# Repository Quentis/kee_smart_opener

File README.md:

# kee_smart_opener

## Reference documents

The datasheets and manuals are not stored in the repository, the table below links to the manufacturers' copies.
The one exception is the E07-433M20S user manual, which is hard to find online and is kept in
[`doc/`](doc/E07-433M20S_Usermanual_EN_v1.30.pdf).

| Document | Notes |
|---|---|
| [HCS300 KEELOQ Code Hopping Encoder datasheet](https://ww1.microchip.com/downloads/en/DeviceDoc/21137G.pdf) | Microchip DS21137G |
| [CC1101 Low-Power Sub-1 GHz RF Transceiver datasheet](https://www.ti.com/lit/ds/symlink/cc1101.pdf) | The transceiver on the E07-433M20S module |
| [RP2350 datasheet](https://datasheets.raspberrypi.com/rp2350/rp2350-datasheet.pdf) | MCU of `sw/kso-fw-rs` |
| [EFR32FG23 Wireless SoC Family Data Sheet](https://www.silabs.com/documents/public/data-sheets/efr32fg23-datasheet.pdf) | Rev. 1.4, SoC of `sw/efr32fg23` |
| [EFR32xG23 Wireless SoC Reference Manual](https://www.silabs.com/documents/public/reference-manuals/efr32xg23-rm.pdf) | Rev. 1.1 |
| [BRD4002A Wireless Pro Kit Mainboard schematic](https://www.silabs.com/documents/public/schematic-files/BRD4002A-A07-schematic.pdf) | Rev. A07 |
| [BRD4265B EFR32FG23B Radio Board (434 MHz, 10 dBm) schematic](https://www.silabs.com/documents/public/schematic-files/BRD4265B-A00-schematic.pdf) | Rev. A00, the copy that was in the repository was A01 |

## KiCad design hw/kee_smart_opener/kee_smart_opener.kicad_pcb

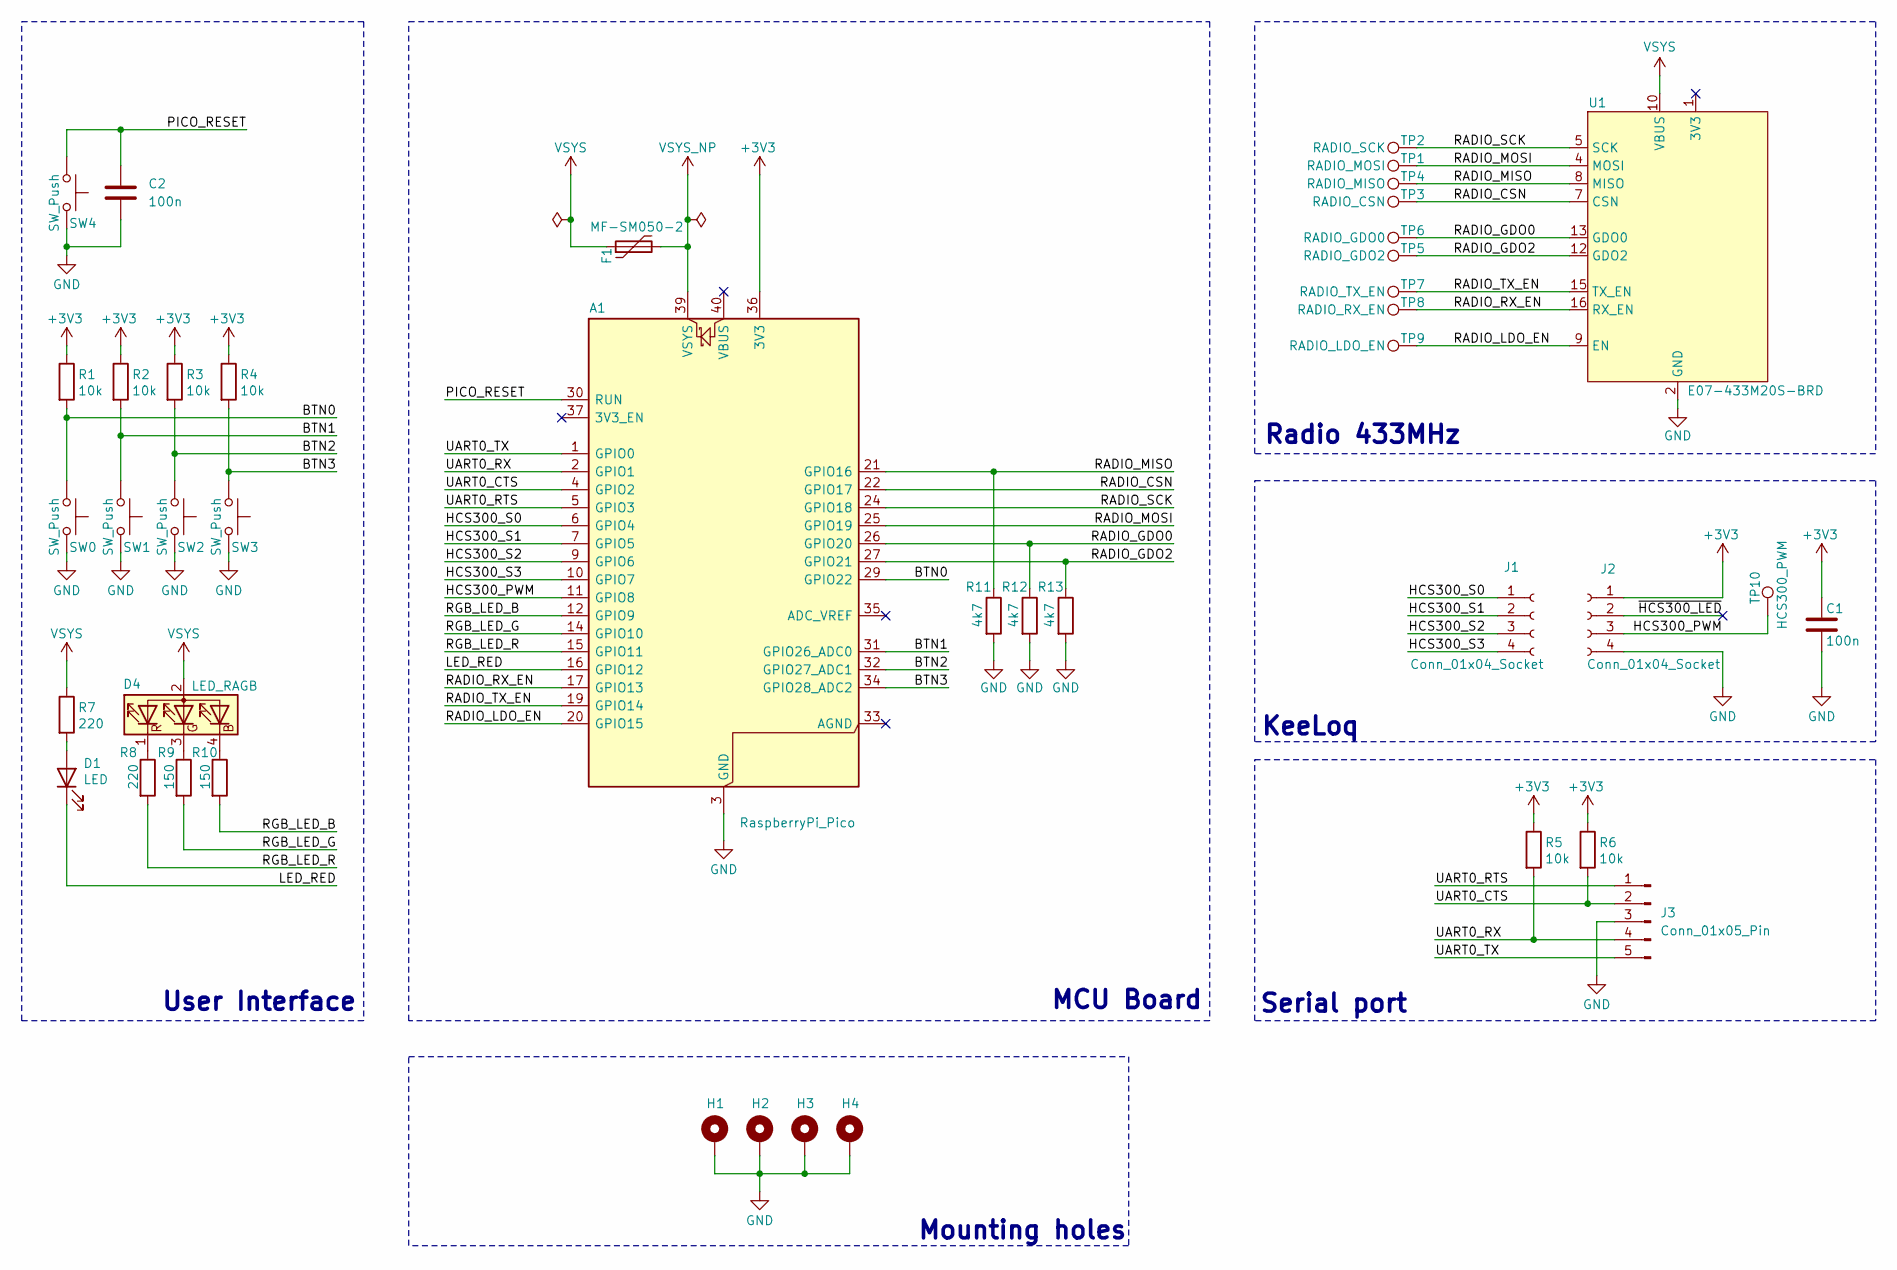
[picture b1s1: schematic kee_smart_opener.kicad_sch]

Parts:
A1: RaspberryPi_Pico; RaspberryPi_Pico_Common_THT
C1, C2: 100n; C_0603_1608Metric_Pad1.08x0.95mm_HandSolder
D1: LED; LED_D5.0mm
D4: LED_RAGB; LED_D5.0mm-4_RGB
F1: MF-SM050-2; Fuse_Bourns_MF-SM_7.98x5.44mm
H1, H2, H3, H4: MountingHole_Pad; MountingHole_3.5mm_Pad_Via
J1, J2: Conn_01x04_Socket; PinSocket_1x04_P2.54mm_Vertical
J3: Conn_01x05_Pin; PinHeader_1x05_P2.54mm_Horizontal
R1, R2, R3, R4, R5, R6: 10k; R_0603_1608Metric_Pad0.98x0.95mm_HandSolder
R7, R8: 220; R_0603_1608Metric_Pad0.98x0.95mm_HandSolder
R9, R10: 150; R_0603_1608Metric_Pad0.98x0.95mm_HandSolder
R11, R12, R13: 4k7; R_0603_1608Metric_Pad0.98x0.95mm_HandSolder
SW0, SW1, SW2, SW3, SW4: SW_Push; SW_B3F-3100
TP1: RADIO_MOSI; TestPoint_Pad_D1.5mm
TP2: RADIO_SCK; TestPoint_Pad_D1.5mm
TP3: RADIO_CSN; TestPoint_Pad_D1.5mm
TP4: RADIO_MISO; TestPoint_Pad_D1.5mm
TP5: RADIO_GDO2; TestPoint_Pad_D1.5mm
TP6: RADIO_GDO0; TestPoint_Pad_D1.5mm
TP7: RADIO_TX_EN; TestPoint_Pad_D1.5mm
TP8: RADIO_RX_EN; TestPoint_Pad_D1.5mm
TP9: RADIO_LDO_EN; TestPoint_Pad_D1.5mm
TP10: HCS300_PWM; TestPoint_Pad_D1.5mm
U1: E07-433M20S-BRD

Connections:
+3V3: A1.36 (3V3), C1.1, J2.1, R1.1, R2.1, R3.1, R4.1, R5.1, R6.1
/BTN0: A1.29 (GPIO22), R1.2, SW0.2
/BTN1: A1.31 (GPIO26_ADC0), R2.2, SW1.2
/BTN2: A1.32 (GPIO27_ADC1), R3.2, SW2.2
/BTN3: A1.34 (GPIO28_ADC2), R4.2, SW3.2
/HCS300_PWM: A1.11 (GPIO8), J2.3, TP10.1 (1_1)
/HCS300_S0: A1.6 (GPIO4), J1.1
/HCS300_S1: A1.7 (GPIO5), J1.2
/HCS300_S2: A1.9 (GPIO6), J1.3
/HCS300_S3: A1.10 (GPIO7), J1.4
/LED_RED: A1.16 (GPIO12), D1.1 (K)
/PICO_RESET: A1.30 (RUN), C2.1, SW4.2
/RADIO_CSN: A1.22 (GPIO17), TP3.1 (1_1), U1.7 (CSN)
/RADIO_GDO0: A1.26 (GPIO20), R12.1, TP6.1 (1_1), U1.13 (GDO0)
/RADIO_GDO2: A1.27 (GPIO21), R13.1, TP5.1 (1_1), U1.12 (GDO2)
/RADIO_LDO_EN: A1.20 (GPIO15), TP9.1 (1_1), U1.9 (EN)
/RADIO_MISO: A1.21 (GPIO16), R11.1, TP4.1 (1_1), U1.8 (MISO)
/RADIO_MOSI: A1.25 (GPIO19), TP1.1 (1_1), U1.4 (MOSI)
/RADIO_RX_EN: A1.17 (GPIO13), TP8.1 (1_1), U1.16 (RX_EN)
/RADIO_SCK: A1.24 (GPIO18), TP2.1 (1_1), U1.5 (SCK)
/RADIO_TX_EN: A1.19 (GPIO14), TP7.1 (1_1), U1.15 (TX_EN)
/RGB_LED_B: A1.12 (GPIO9), R10.2
/RGB_LED_G: A1.14 (GPIO10), R9.2
/RGB_LED_R: A1.15 (GPIO11), R8.2
/UART0_CTS: A1.4 (GPIO2), J3.2, R6.2
/UART0_RTS: A1.5 (GPIO3), J3.1
/UART0_RX: A1.2 (GPIO1), J3.4, R5.2
/UART0_TX: A1.1 (GPIO0), J3.5
/~HCS300_LED: J2.2
GND: A1.3 (GND), A1.8 (GND), A1.13 (GND), A1.18 (GND), A1.23 (GND), A1.28 (GND), A1.38 (GND), C1.2, C2.2, H1.1 (1_1), H2.1 (1_1), H3.1 (1_1), H4.1 (1_1), J2.4, J3.3, R11.2, R12.2, R13.2, SW0.1, SW1.1, SW2.1, SW3.1, SW4.1, U1.2 (GND), U1.3 (GND), U1.6 (GND), U1.11 (GND), U1.14 (GND)
unnamed: D1.2 (A), R7.2
unnamed: D4.4 (BK), R10.1
unnamed: D4.3 (GK), R9.1
unnamed: D4.1 (RK), R8.1
VSYS: D4.2 (A), F1.1, R7.1, U1.10 (VBUS)
VSYS_NP: A1.39 (VSYS), F1.2

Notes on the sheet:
Serial port
Radio 433MHz
User Interface
KeeLoq
Mounting holes
MCU Board

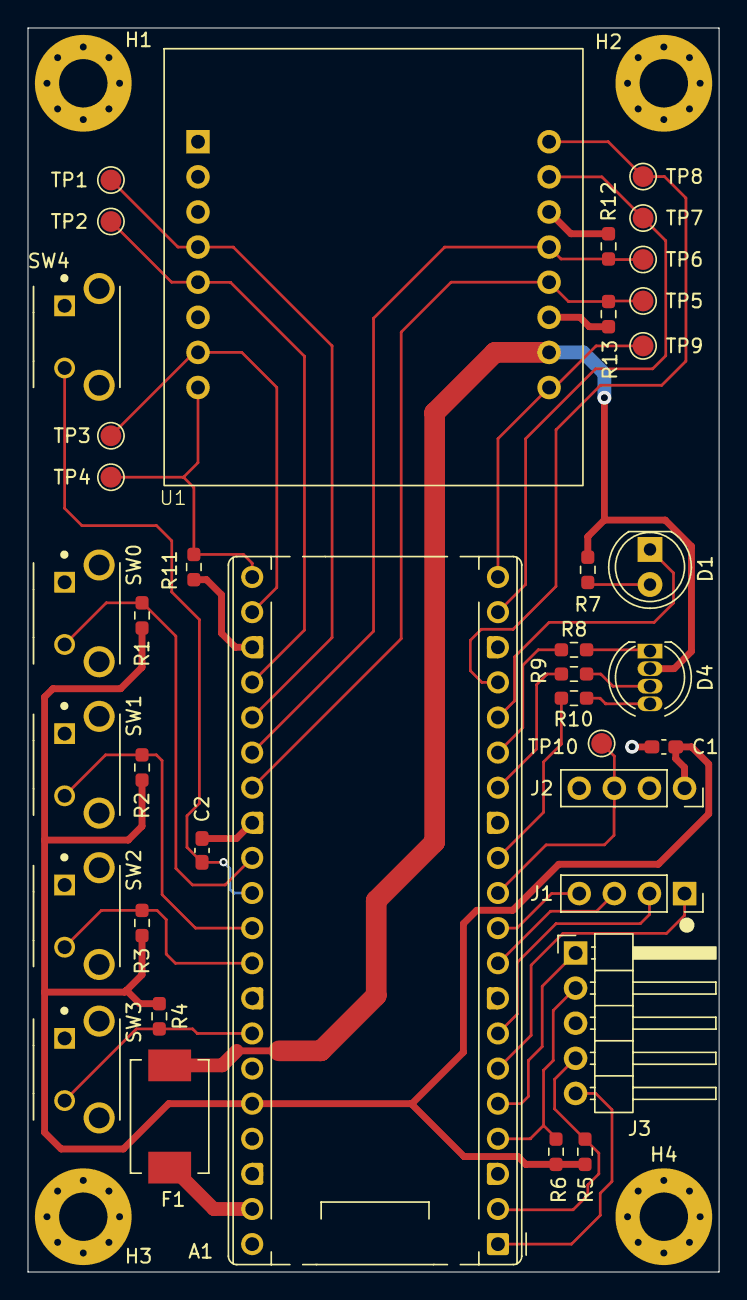
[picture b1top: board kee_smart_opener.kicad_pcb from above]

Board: 2 copper layers, 50.0 x 90.0 mm, 42 parts (0 on the bottom side), 35 nets.

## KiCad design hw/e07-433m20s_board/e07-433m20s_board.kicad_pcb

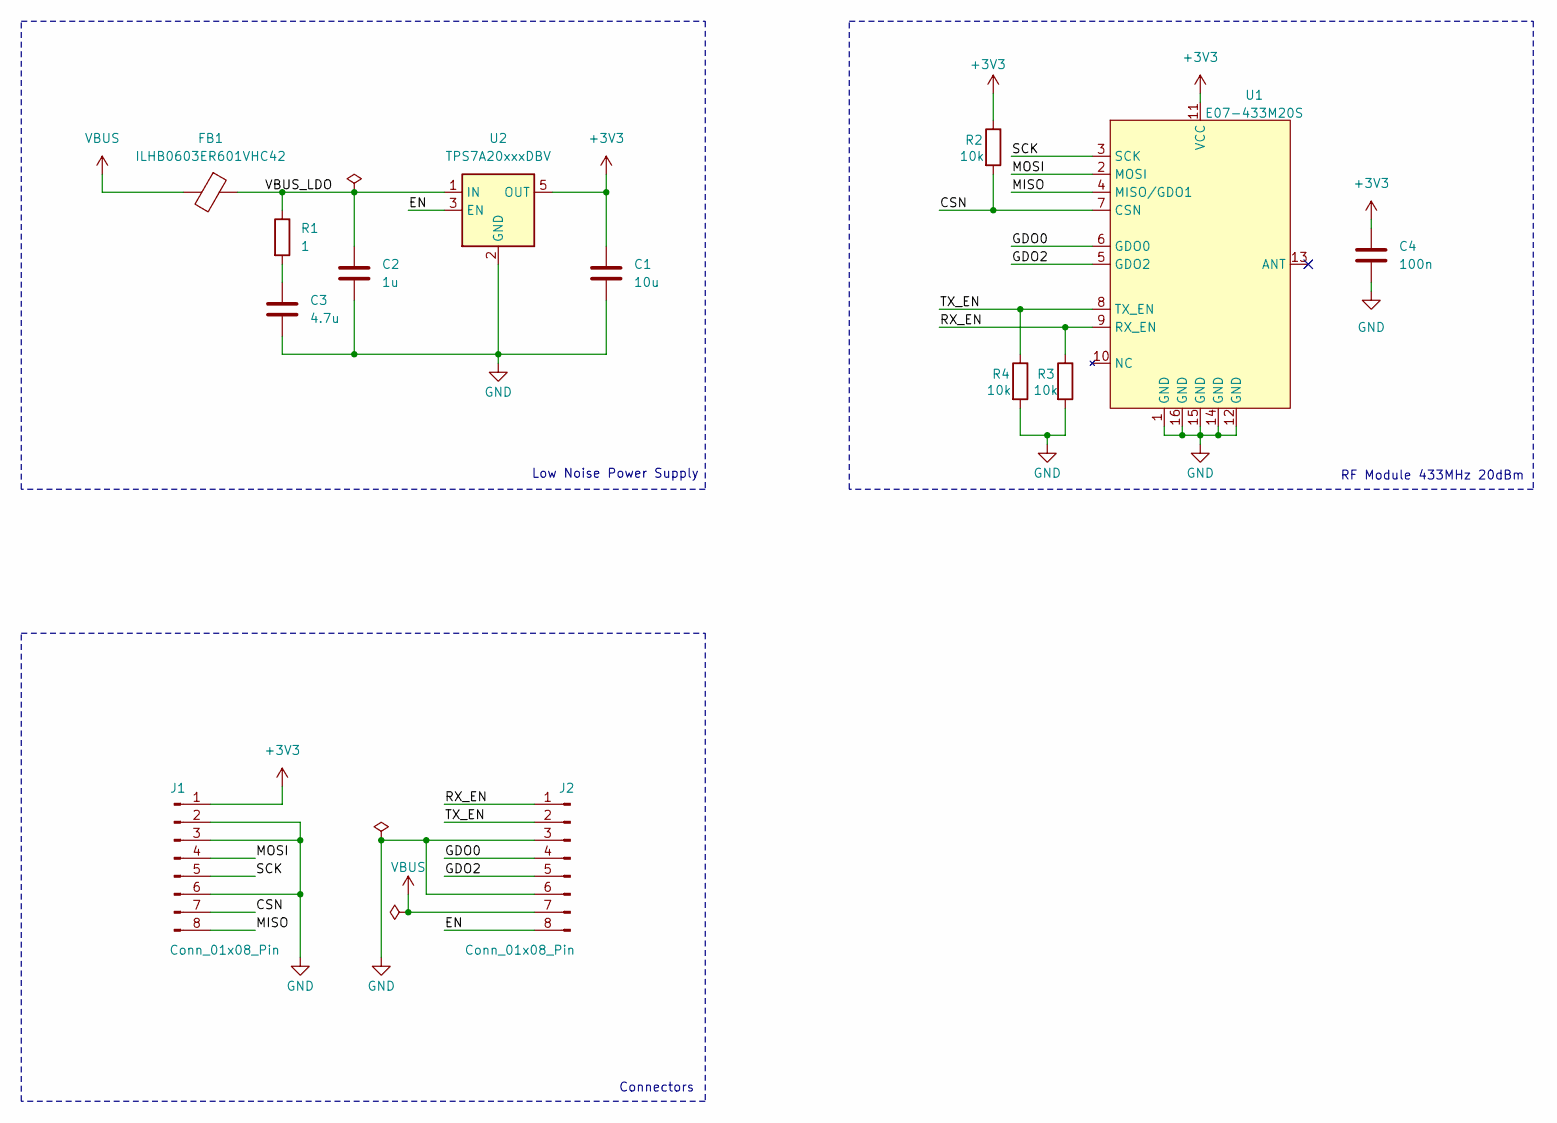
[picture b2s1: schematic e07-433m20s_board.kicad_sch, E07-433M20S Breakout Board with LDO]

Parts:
C1: 10u; C_0805_2012Metric_Pad1.18x1.45mm_HandSolder
C2: 1u; C_0603_1608Metric_Pad1.08x0.95mm_HandSolder
C3: 4.7u; C_0805_2012Metric_Pad1.18x1.45mm_HandSolder
C4: 100n; C_0603_1608Metric_Pad1.08x0.95mm_HandSolder
FB1: ILHB0603ER601VHC42; L_0603_1608Metric
J1, J2: Conn_01x08_Pin; PinHeader_1x08_P2.54mm_Vertical
R1: 1; R_0603_1608Metric_Pad0.98x0.95mm_HandSolder
R2, R3, R4: 10k; R_0603_1608Metric_Pad0.98x0.95mm_HandSolder
U1: E07-433M20S
U2: TPS7A20xxxDBV; SOT-23-5

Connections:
+3V3: C1.1, C4.1, J1.1, R2.1, U1.11 (VCC), U2.5 (OUT)
/CSN: J1.7, R2.2, U1.7 (CSN)
/EN: J2.8, U2.3 (EN)
/GDO0: J2.4, U1.6 (GDO0)
/GDO2: J2.5, U1.5 (GDO2)
/MISO: J1.8, U1.4 (MISO/GDO1)
/MOSI: J1.4, U1.2 (MOSI)
/RX_EN: J2.1, R3.1, U1.9 (RX_EN)
/SCK: J1.5, U1.3 (SCK)
/TX_EN: J2.2, R4.1, U1.8 (TX_EN)
/VBUS_LDO: C2.1, FB1.1, R1.1, U2.1 (IN)
GND: C1.2, C2.2, C3.2, C4.2, J1.2, J1.3, J1.6, J2.3, J2.6, R3.2, R4.2, U1.1 (GND), U1.12 (GND), U1.14 (GND), U1.15 (GND), U1.16 (GND), U2.2 (GND)
unnamed: C3.1, R1.2
VBUS: FB1.2, J2.7

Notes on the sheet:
Connectors
RF Module 433MHz 20dBm
Low Noise Power Supply

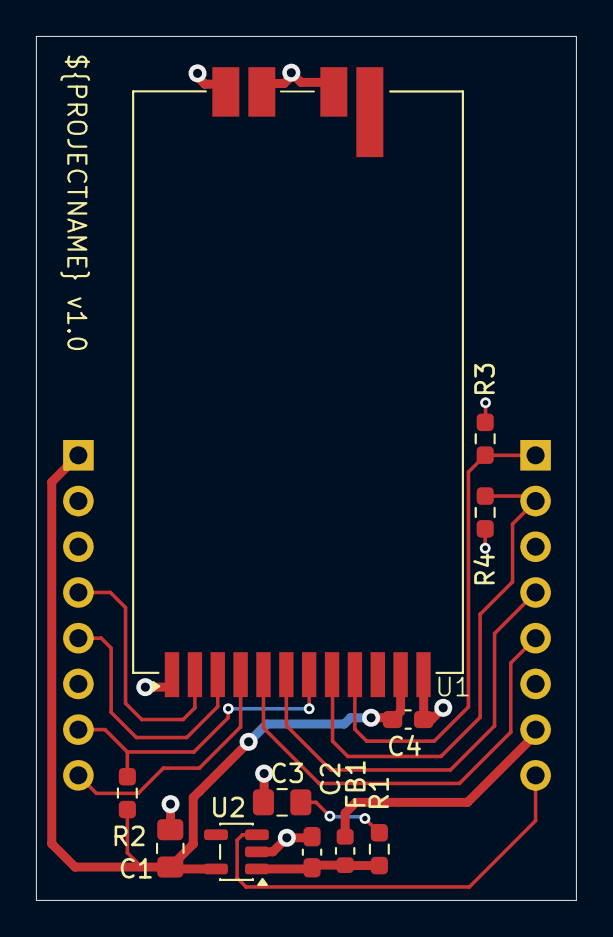
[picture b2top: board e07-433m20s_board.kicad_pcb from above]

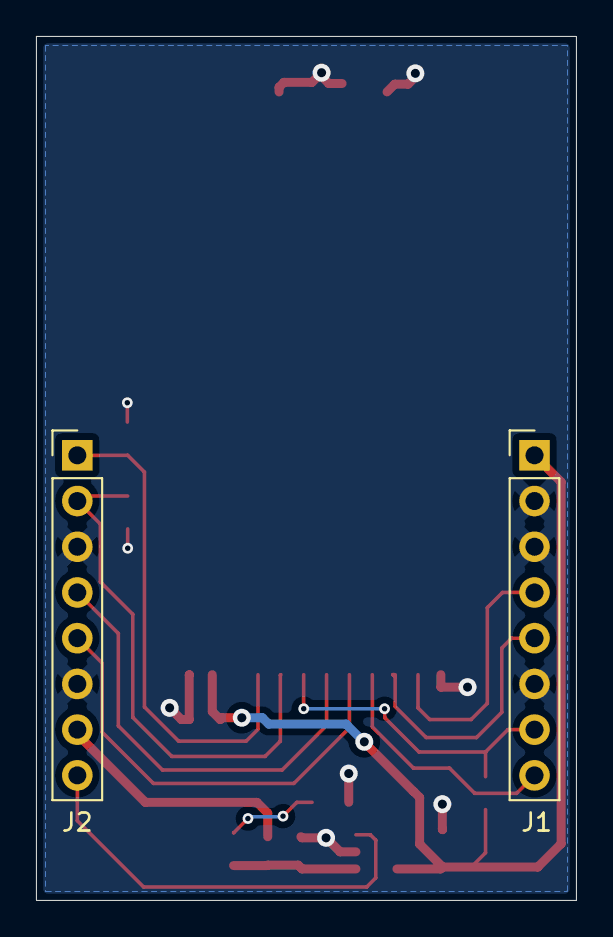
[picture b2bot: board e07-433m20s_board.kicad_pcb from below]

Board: 2 copper layers, 30.0 x 48.0 mm, 13 parts (2 on the bottom side), 14 nets.

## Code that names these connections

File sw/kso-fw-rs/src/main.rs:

#![no_std]
#![no_main]
#![allow(unused)]

use cc1101_embassy::{Cc1101, Modulation, PacketLength, RadioConfig, SyncMode, TxPower};
use defmt as _;
use defmt::{debug, error, info, warn};
use defmt_rtt as _;
use embassy_embedded_hal::shared_bus::asynch::spi::SpiDevice;
use embassy_executor::Spawner;
use embassy_rp::gpio::{Input, Level, Output, Pull};
use embassy_rp::peripherals::{DMA_CH0, DMA_CH1, PIO0};
use embassy_rp::pio::program::pio_file;
use embassy_rp::pio::{Common, FifoJoin, Pio, PioPin, StateMachine};
use embassy_rp::pio_programs::clock_divider::calculate_pio_clock_divider;
use embassy_rp::spi::{self, Phase, Polarity, Spi};
use embassy_rp::{Peri, binary_info, pio};
use embassy_rp::{bind_interrupts, dma};
use embassy_sync::blocking_mutex::raw::NoopRawMutex;
use embassy_sync::mutex::Mutex;
use embassy_time::{Instant, Timer};
use embedded_hal_async::spi::{Operation, SpiDevice as _};
use fugit::{ExtU32, Hertz, HertzU32, RateExtU32};
use panic_probe as _;
use static_cell::StaticCell;

mod hcs300;
use hcs300::{Hcs300Decoder, Hcs300Packet};

use crate::hcs300::{Hcs300ButtonStatus, Hcs300SerialNumber};

type AsyncSpi0 = Spi<'static, embassy_rp::peripherals::SPI0, spi::Async>;

static SPI_BUS: StaticCell<Mutex<NoopRawMutex, AsyncSpi0>> = StaticCell::new();

bind_interrupts!(struct Irqs {
    DMA_IRQ_0 => dma::InterruptHandler<DMA_CH0>, dma::InterruptHandler<DMA_CH1>;
    PIO0_IRQ_0 => pio::InterruptHandler<PIO0>;
});

/// Idle/stuck timeout of the HCS300 PIO program in ticks (1 tick = 1 us). Has to be longer than the
/// longest legitimate pulse, which is the header (10 TE, up to 6.6 ms).
const HCS300_TIMEOUT_TICKS: u32 = 10_000;

/// Word pushed by the HCS300 PIO program when the line was idle or stuck for the whole timeout
const HCS300_PIO_SENTINEL: u32 = u32::MAX;

/// Measures the high and low pulses of the HCS300 PWM output.
///
/// For every edge one word is pushed to the RX FIFO: the ticks left of the timeout counter, so the
/// pulse duration is `HCS300_TIMEOUT_TICKS - word`. If the line stays at one level for the whole
/// timeout, `HCS300_PIO_SENTINEL` is pushed instead (and a stuck high line is waited out).
///
/// The program and its cycle budget are in `pio/hcs300_capture.pio`. One tick is 5 PIO cycles (5 MHz
/// clock). The simulation tests in `test/sim/pio` read the same file.
fn setup_pio_task_sm0<'d>(
    pio: &mut Common<'d, PIO0>,
    sm: &mut StateMachine<'d, PIO0, 0>,
    hcs300_pwm_pin: Peri<'d, impl PioPin>,
) {
    let prog = pio_file!("pio/hcs300_capture.pio");
    let mut cfg = pio::Config::default();
    let loaded_prog = &pio.load_program(&prog.program);
    debug!("HCS300 PIO0 origin: {}", loaded_prog.origin);
    cfg.use_program(loaded_prog, &[]);
    let in_pin = pio.make_pio_pin(hcs300_pwm_pin);
    cfg.set_in_pins(&[&in_pin]);
    cfg.set_jmp_pin(&in_pin);
    cfg.clock_divider = calculate_pio_clock_divider(5_000_000);
    sm.set_config(&cfg);
}

#[embassy_executor::task]
async fn pio_task_sm0(mut sm: StateMachine<'static, PIO0, 0>) {
    sm.set_enable(true);

    sm.tx().push(HCS300_TIMEOUT_TICKS);
    let mut decoder = Hcs300Decoder::new();
    loop {
        let word = sm.rx().wait_pull().await;
        if word == HCS300_PIO_SENTINEL {
            decoder.reset();
            continue;
        }

        let ticks = HCS300_TIMEOUT_TICKS.saturating_sub(word);
        if let Some(packet) = decoder.push(ticks) {
            info!(
                "HCS300: serial {=u32:08x}, buttons {=u8:04b}, vlow {}, repeat {}, encrypted {=u32:08x}, TE {} us",
                packet.serial_number.get(),
                packet.button_status.get(),
                packet.vlow,
                packet.repeat,
                packet.encrypted,
                decoder.te()
            );
        }
    }
}

#[embassy_executor::main]
async fn main(spawner: Spawner) {
    info!("Starting...");
    let p = embassy_rp::init(Default::default());

    // let mut led_rgb_blue = Output::new(p.PIN_9, Level::Low);
    // let mut led_rgb_green = Output::new(p.PIN_10, Level::Low);
    // let mut led_rgb_red = Output::new(p.PIN_11, Level::Low);

    // let mut led_err_red = Output::new(p.PIN_12, Level::Low);

    let mut led_run_green = Output::new(p.PIN_25, Level::High);

    // Configure HCS300 pins
    let mut hcs300_pwm_pin = p.PIN_8;
    let mut pio = Pio::new(p.PIO0, Irqs);

    // // Configure CC1101 pins
    // let mut cc1101_en = Output::new(p.PIN_15, Level::Low);
    // let mut cc1101_tx_en = Output::new(p.PIN_14, Level::Low);
    // let mut cc1101_rx_en = Output::new(p.PIN_13, Level::Low);

    // let mut spi_config = spi::Config::default();
    // spi_config.frequency = 1_000_000;
    // spi_config.phase = Phase::CaptureOnFirstTransition;
    // spi_config.polarity = Polarity::IdleLow;

    // let cs = Output::new(p.PIN_17, Level::High);

    // // Enable the LDO on e07-433m20s_board (C1101 chip)
    // cc1101_en.set_high();

    // let spi_bus = Spi::new(
    //     p.SPI0, p.PIN_18, p.PIN_19, p.PIN_16, p.DMA_CH0, p.DMA_CH1, Irqs, spi_config,
    // );
    // let spi_bus = SPI_BUS.init(Mutex::new(spi_bus));
    // let mut spi_dev = SpiDevice::new(spi_bus, cs);

    // let mut btn0 = Input::new(p.PIN_22, Pull::None);

    // let gdo0 = Input::new(p.PIN_20, Pull::None);
    // let gdo2 = Input::new(p.PIN_21, Pull::None);

    // let packet = Hcs300Packet {
    //     encrypted: 0,
    //     serial_number: Hcs300SerialNumber::new(0).unwrap(),
    //     button_status: Hcs300ButtonStatus::new(0).unwrap(),
    //     vlow: false,
    //     repeat: false,
    // };
    // let mut encoded_packet = [0; Hcs300Packet::CODEWORD_BYTES];
    // packet
    //     .encode(&mut encoded_packet)
    //     .expect("Keeloq packet encoding failed!");

    // let mut cc1101 = match Cc1101::new(spi_dev, gdo0, gdo2).await {
    //     Ok(dev) => dev,
    //     Err(e) => {
    //         error!("CC1101 init failed: {:?}", e);
    //         loop {
    //             Timer::after_millis(1000).await;
    //         }
    //     }
    // };

    // let radio_config = RadioConfig::new()
    //     .frequency_hz(433_920_000)
    //     .baud_rate(2500)
    //     .modulation(Modulation::Ook)
    //     .sync_mode(SyncMode::None)
    //     .sync_word(0xD391)
    //     .packet_length(PacketLength::Fixed(Hcs300Packet::CODEWORD_BYTES as u8))
    //     .append_status(false)
    //     .crc_enable(false)
    //     .tx_power(TxPower::DbmMinus10);

    // if let Err(spi_err) = cc1101.configure(&radio_config).await {
    //     error!("SPI error during configure: {:?}", spi_err);
    //     loop {
    //         Timer::after_millis(1000).await;
    //     }
    // }

    // if let Err(err) = cc1101.idle().await {
    //     error!("Error during idle transition: {:?}", err)
    // }

    setup_pio_task_sm0(&mut pio.common, &mut pio.sm0, hcs300_pwm_pin);
    spawner.spawn(pio_task_sm0(pio.sm0).unwrap());

    loop {
        // btn0.wait_for_low().await;
        // info!("Button 0 pressed");
        // btn0.wait_for_high().await;

        //     let mut buf = [0u8; 1];
        //     spi_dev
        //         .transaction(&mut [
        //             Operation::Write(&[0x31 | 0x80 | 0x40]),
        //             Operation::Read(&mut buf),
        //         ])
        //         .await
        //         .unwrap();
        //     info!("Version number: {}", buf);
        // Timer::after_millis(100).await;
        // let test_packet = [0x55; 5];

        // Test cc1101
        // cc1101_tx_en.set_high();
        // Timer::after_millis(10).await;
        // let tx_start = Instant::now();
        // let tx_result = cc1101.transmit(&encoded_packet[..]).await;
        // info!("transmit took {} ms", tx_start.elapsed().as_millis());
        // match tx_result {
        //     Ok(()) => {
        //         info!("Keeloq packet transmitted: {=[u8]:02x}", encoded_packet[..])
        //     }
        //     Err(err) => {
        //         error!("Error during transmission: {:?}", err)
        //     }
        // }
        // Timer::after_millis(10).await;
        // cc1101_tx_en.set_low();

        // if let Err(err) = cc1101.idle().await {
        //     error!("Error during idle transition: {:?}", err)
        // }

        // Timer::after_millis(100).await;
        // cc1101_tx_en.set_low();

        Timer::after_millis(3000).await;
    }

    // Configure button pins
    // let mut btn0_pin = pins.gpio22.into_floating_input();
    // let mut btn1_pin = pins.gpio26.into_floating_input();
    // let mut btn2_pin = pins.gpio27.into_floating_input();
    // let mut btn3_pin = pins.gpio28.into_floating_input();
}

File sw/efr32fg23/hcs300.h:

#ifndef HCS300_H
#define HCS300_H

#include <stdint.h>
#include <stdbool.h>

#include "sl_status.h"

// HCS300 protocol parameters
// All timings values are integer multiples of TE.
// TE is configurable between: 100us, 200us, 400us.
// Packet:
//   - Preamble: 23 TE (12 sync pulses) - 50% duty cycle
//   - Header: 10 TE gap
//   - Data: 66 bits -> 1 bit is 3 TE (PWM modulated)
//     - 0 bit: 2 TE high, 1 TE low
//     - 1 bit: 1 TE high, 2 TE low

// 50% duty cycle preamble
#define HCS300_PREAMBLE_TE            23

// Gap between preamble and data
#define HCS300_HEADER_GAP_TE          10

// Serial number, button code, VLOW and RPT bits
#define HCS300_FIXED_BITS             34
#define HCS300_ENCRYPTED_BITS         32
#define HCS300_BIT_TE                  3

// Data portion of code word (66 bits)
#define HCS300_DATA_BITS              (HCS300_ENCRYPTED_BITS + HCS300_FIXED_BITS)

// Total code word data length in TE units (each bit is encoded in 3 TE - PWM modulated)
#define HCS300_DATA_BITS_TE         (HCS300_DATA_BITS * HCS300_BIT_TE)

#define HCS300_CODEWORD_DATA_BYTES  ((HCS300_DATA_BITS_TE + 7) >> 3)
#define HCS300_CODEWORD_BYTES       ((HCS300_PREAMBLE_TE    \
                                    + HCS300_HEADER_GAP_TE  \
                                    + HCS300_DATA_BITS_TE + 7) >> 3)

// Button status getter macros
#define HCS300_BTN_STATUS_S0(btn_status)  ((btn_status) & HCS300_S0)
#define HCS300_BTN_STATUS_S1(btn_status)  ((btn_status) & HCS300_S1)
#define HCS300_BTN_STATUS_S2(btn_status)  ((btn_status) & HCS300_S2)
#define HCS300_BTN_STATUS_S3(btn_status)  ((btn_status) & HCS300_S3)

// The button inputs of HCS300 chip shall be activated to receive pwm signal.
typedef enum hcs300_sw_id {
  HCS300_S0 = 0x1,
  HCS300_S1 = 0x2,
  HCS300_S2 = 0x4,
  HCS300_S3 = 0x8,
} hcs300_sw_id_t;

sl_status_t hcs300_init(void);
sl_status_t hcs300_deinit(void);
sl_status_t hcs300_activate(hcs300_sw_id_t sw, bool repeat);
void hcs300_step(void);

void hcs300_proceed_cb(void);

sl_status_t hcs300_create_codeword(uint16_t hcs300_id,
                                   uint8_t *codeword,
                                   uint16_t *codeword_len,
                                   bool rpt,
                                   bool vlow,
                                   uint8_t btn_status,
                                   uint32_t serial,
                                   uint32_t encrypted);

sl_status_t hcs300_create_codeword_data(uint16_t hcs300_id,
                                        uint8_t *codeword,
                                        uint16_t *codeword_len,
                                        bool rpt,
                                        bool vlow,
                                        uint8_t btn_status,
                                        uint32_t serial,
                                        uint32_t encrypted);

void hcs300_on_rx_packet(uint16_t hcs300_id,
                         bool rpt,
                         bool vlow,
                         uint8_t btn_status,
                         uint32_t serial,
                         uint32_t encrypted);
#endif // HCS300_H

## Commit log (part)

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2025-10-31 Generate rail_soc_empty project
    The project is created from simplicity_sdk_2025.6.2 version.
    The project is created with copy import mode to export the simplicity
    SDK files which makes easier to humans to use VS code workspace
    for all code in the project. This way the AI agents can search in SDK
    code as well.
    The SDK files are not committed because those can be generated
2025-12-17 Add hcs300 timer irq-based processing
2025-12-17 Add mcu, hcs300, board docs
2025-12-17 Add vscode files
2025-12-17 Extend readme with rtl_433-rtlsdr measurements
2026-06-21 Add qg_kicad_lib submodule
2026-06-21 Move silabs code to sw/efr32fg23
